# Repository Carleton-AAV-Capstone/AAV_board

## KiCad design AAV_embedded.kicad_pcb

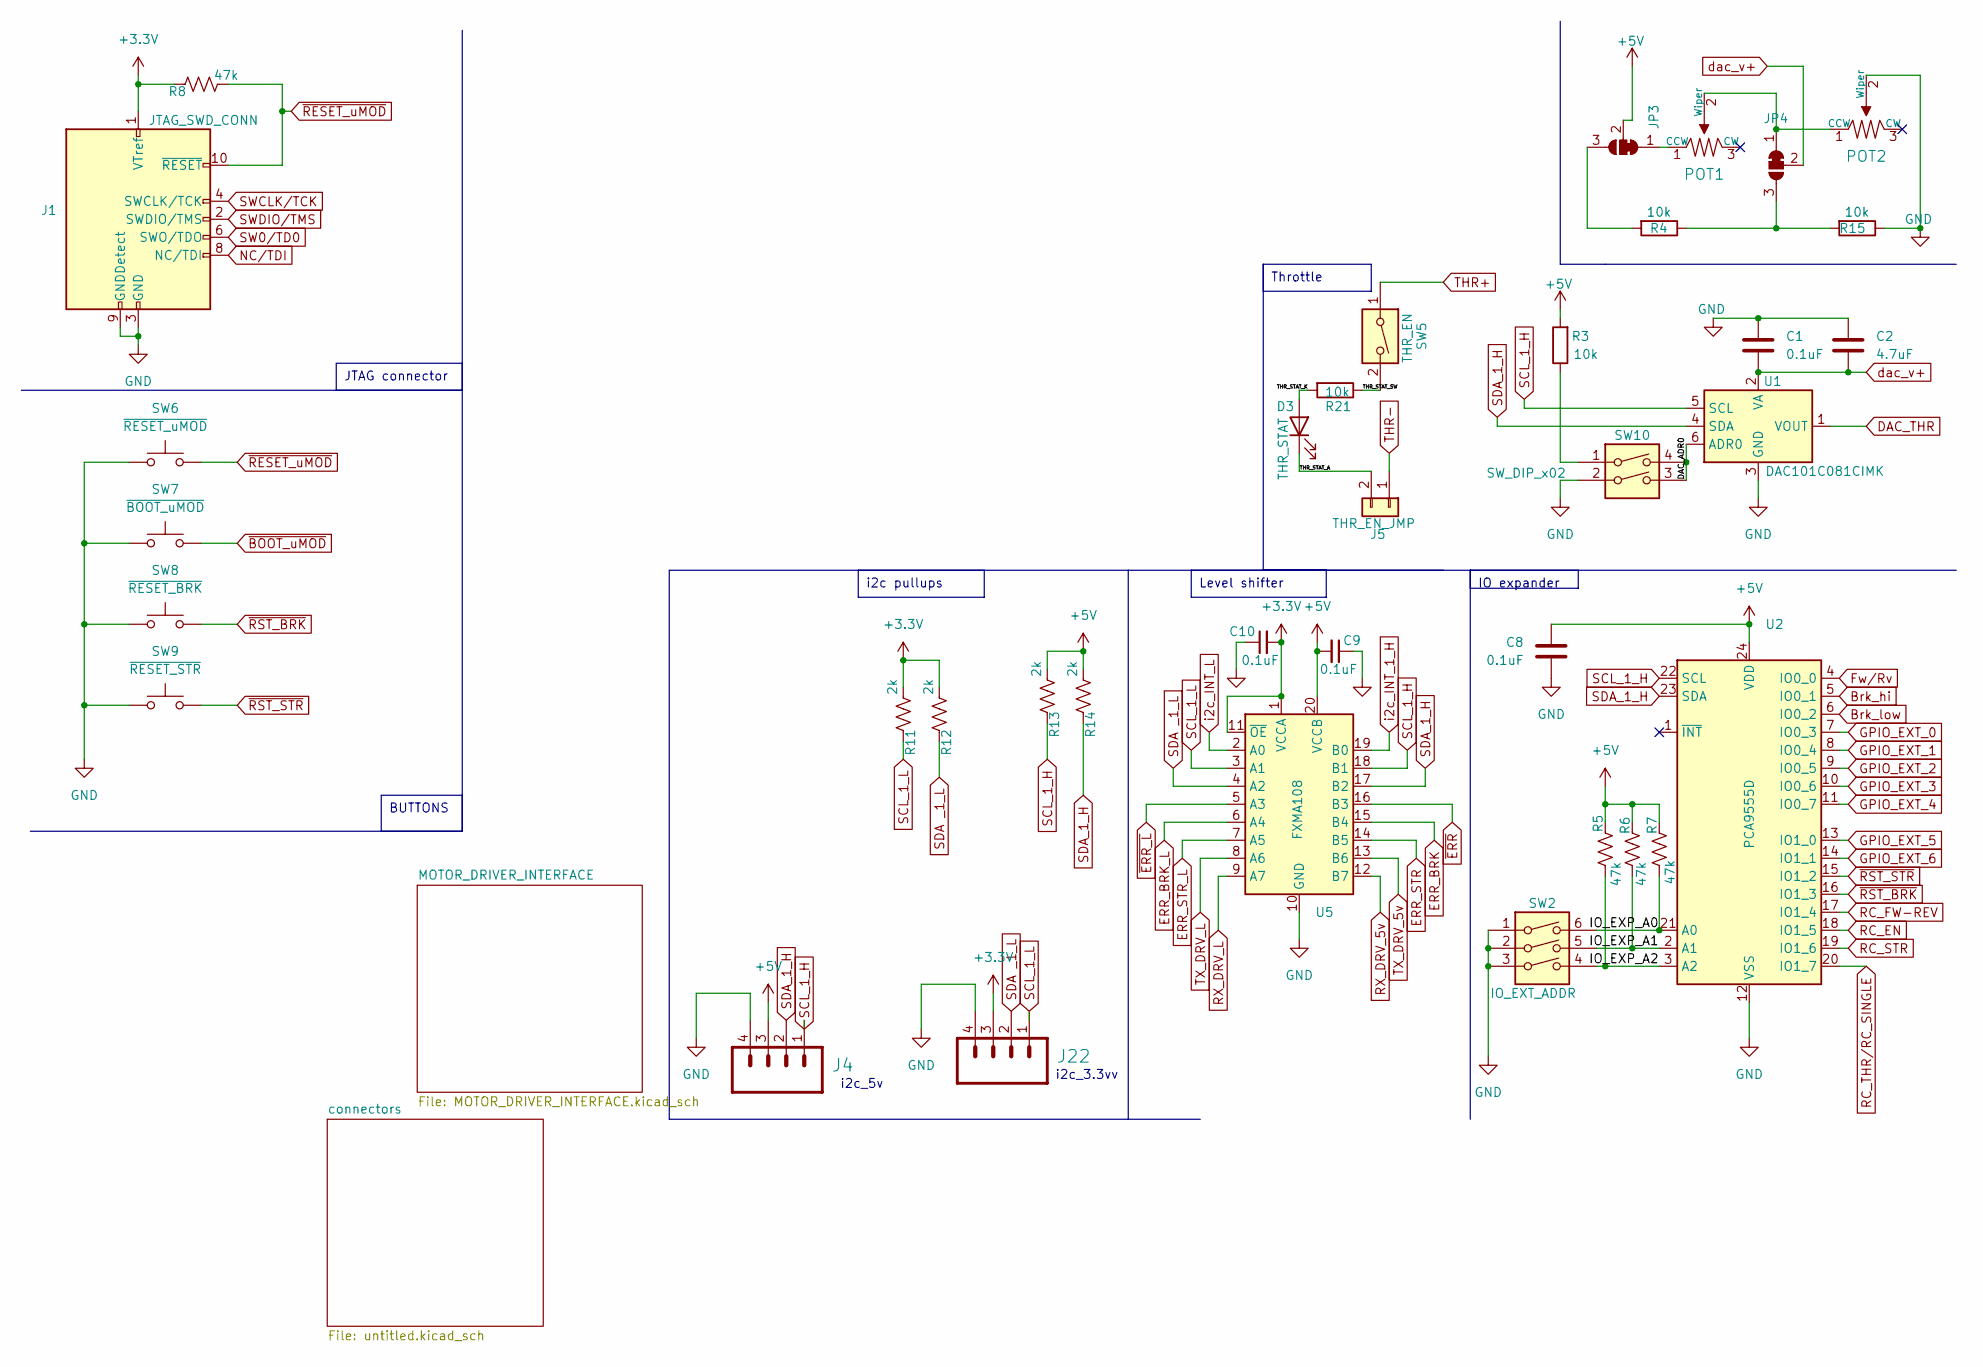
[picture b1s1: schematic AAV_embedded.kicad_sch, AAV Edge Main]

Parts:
C1, C8, C9, C10: 0.1uF; C_1206_3216Metric
C2: 4.7uF; C_1206_3216Metric
D3: THR_STAT; LED_0805_2012Metric
J1: JTAG_SWD_CONN; PinHeader_2x05_P1.27mm_Horizontal
J4, J22: JST-4-PTH
J5: THR_EN_JMP; PinHeader_1x02_P1.27mm_Horizontal; Part Number 1-0201FBV0T
JP3: POT_HIGH_BYPASS; SolderJumper-3_P1.3mm_Bridged12_Pad1.0x1.5mm
JP4: POT_LOW_BYPASS; SolderJumper-3_P1.3mm_Bridged12_Pad1.0x1.5mm
POT1, POT2: TC33X-2-103E; Potentiometer_Bourns_3266W_Vertical; MPN TC33X-2-103E; Digi-Key_PN TC33X-103ETR-ND
R3, R4, R15, R21: 10k; R_1206_3216Metric
R5, R6, R7, R8: 47k; R_1206_3216Metric
R11, R12, R13, R14: 2k; R_1206_3216Metric
SW2: IO_EXT_ADDR; SW_DIP_SPSTx03_Slide_6.7x9.18mm_W6.73mm_P2.54mm_LowProfile_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
SW5: THR_EN; SW_DIP_SPSTx01_Slide_6.7x4.1mm_W6.73mm_P2.54mm_LowProfile_J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
SW6: ~{RESET_uMOD}; SW_Push_SPST_NO_Alps_SKRK
SW7: ~{BOOT_uMOD}; SW_Push_SPST_NO_Alps_SKRK
SW8: ~{RESET_BRK}; SW_Push_SPST_NO_Alps_SKRK
SW9: ~{RESET_STR}; SW_Push_SPST_NO_Alps_SKRK
SW10: SW_DIP_x02; SW_DIP_SPSTx02_Slide_6.7x6.64mm_W6.73mm_P2.54mm_LowProfile_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
U1: DAC101C081CIMK; SOT-23-6
U2: PCA9555D; SOIC-24W_7.5x15.4mm_P1.27mm
U5: FXMA108; WQFN-20-1EP_2.5x4.5mm_P0.5mm_EP1x2.9mm

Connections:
+3.3V: C10.2, J1.1 (VTref), J22.3, R8.1, R11.2, R12.2, U5.1 (VCCA), U5.11 (~OE); also elsewhere on the board
+5V: C8.2, C9.2, J4.3, JP3.2 (C), R3.2, R5.1, R6.1, R7.1, R13.2, R14.2, U2.24 (VDD), U5.20 (VCCB); also elsewhere on the board
/DAC_ADR0: SW10.3, SW10.4, U1.6 (ADR0)
/IO_EXP_A0: R7.2, SW2.6, U2.21 (A0)
/IO_EXP_A1: R6.2, SW2.5, U2.2 (A1)
/IO_EXP_A2: R5.2, SW2.4, U2.3 (A2)
/THR_STAT_A: D3.1 (K), J5.2
/THR_STAT_K: D3.2 (A), R21.2
/THR_STAT_SW: R21.1, SW5.2
Brk_hi: U2.5 (IO0_1); also elsewhere on the board
Brk_low: U2.6 (IO0_2); also elsewhere on the board
DAC_THR: U1.1 (VOUT); also elsewhere on the board
ERR_BRK: U5.15 (B4); also elsewhere on the board
ERR_BRK_L: U5.6 (A4)
ERR_STR: U5.14 (B5); also elsewhere on the board
ERR_STR_L: U5.7 (A5)
Fw/Rv: U2.4 (IO0_0); also elsewhere on the board
GND: C1.1, C2.1, C8.1, C9.1, C10.1, J1.3 (GND), J1.5 (GND), J1.9 (GNDDetect), J4.4, J22.4, POT2.2 (Wiper), R15.1, SW2.1, SW2.2, SW2.3, SW6.1, SW7.1, SW8.1, SW9.1, SW10.2, U1.3 (GND), U2.12 (VSS), U5.10 (GND); also elsewhere on the board
GPIO_EXT_0: U2.7 (IO0_3); also elsewhere on the board
GPIO_EXT_1: U2.8 (IO0_4); also elsewhere on the board
GPIO_EXT_2: U2.9 (IO0_5); also elsewhere on the board
GPIO_EXT_3: U2.10 (IO0_6); also elsewhere on the board
GPIO_EXT_4: U2.11 (IO0_7); also elsewhere on the board
GPIO_EXT_5: U2.13 (IO1_0); also elsewhere on the board
GPIO_EXT_6: U2.14 (IO1_1)
NC/TDI: J1.8 (NC/TDI)
unnamed: JP3.1 (A), POT1.1 (CCW)
unnamed: JP3.3 (B), R4.2
unnamed: JP4.1 (A), POT1.2 (Wiper), POT2.1 (CCW)
unnamed: JP4.3 (B), R4.1, R15.2
unnamed: R3.1, SW10.1
RC_EN: U2.18 (IO1_5)
RC_FW-REV: U2.17 (IO1_4)
RC_STR: U2.19 (IO1_6)
RC_THR/RC_SINGLE: U2.20 (IO1_7)
RX_DRV_5v: U5.12 (B7); also elsewhere on the board
RX_DRV_L: U5.9 (A7); also elsewhere on the board
SCL_1_H: J4.1, R13.1, U1.5 (SCL), U2.22 (SCL), U5.18 (B1)
SCL_1_L: J22.1, R11.1, U5.3 (A1); also elsewhere on the board
SDA _1_L: J22.2, R12.1, U5.4 (A2); also elsewhere on the board
SDA_1_H: J4.2, R14.1, U1.4 (SDA), U2.23 (SDA), U5.17 (B2)
SW0/TD0: J1.6 (SWO/TDO)
SWCLK/TCK: J1.4 (SWCLK/TCK); also elsewhere on the board
SWDIO/TMS: J1.2 (SWDIO/TMS); also elsewhere on the board
THR+: SW5.1; also elsewhere on the board
THR-: J5.1; also elsewhere on the board
TX_DRV_5v: U5.13 (B6); also elsewhere on the board
TX_DRV_L: U5.8 (A6); also elsewhere on the board
dac_v+: C1.2, C2.2, JP4.2 (C), U1.2 (VA)
i2c_INT_1_H: U5.19 (B0)
i2c_INT_L: U5.2 (A0); also elsewhere on the board
~BOOT_uMOD: SW7.2; also elsewhere on the board
~E-STOP: U5.5 (A3); also elsewhere on the board
~ERR: U5.16 (B3)
~RESET_uMOD: J1.10 (~RESET), R8.2, SW6.2; also elsewhere on the board
~RST_BRK: SW8.2, U2.16 (IO1_3); also elsewhere on the board
~RST_STR: SW9.2, U2.15 (IO1_2); also elsewhere on the board

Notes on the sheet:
Throttle
IO expander
JTAG connector
i2c pullups
Level shifter
BUTTONS
i2c_5v
i2c_3.3vv

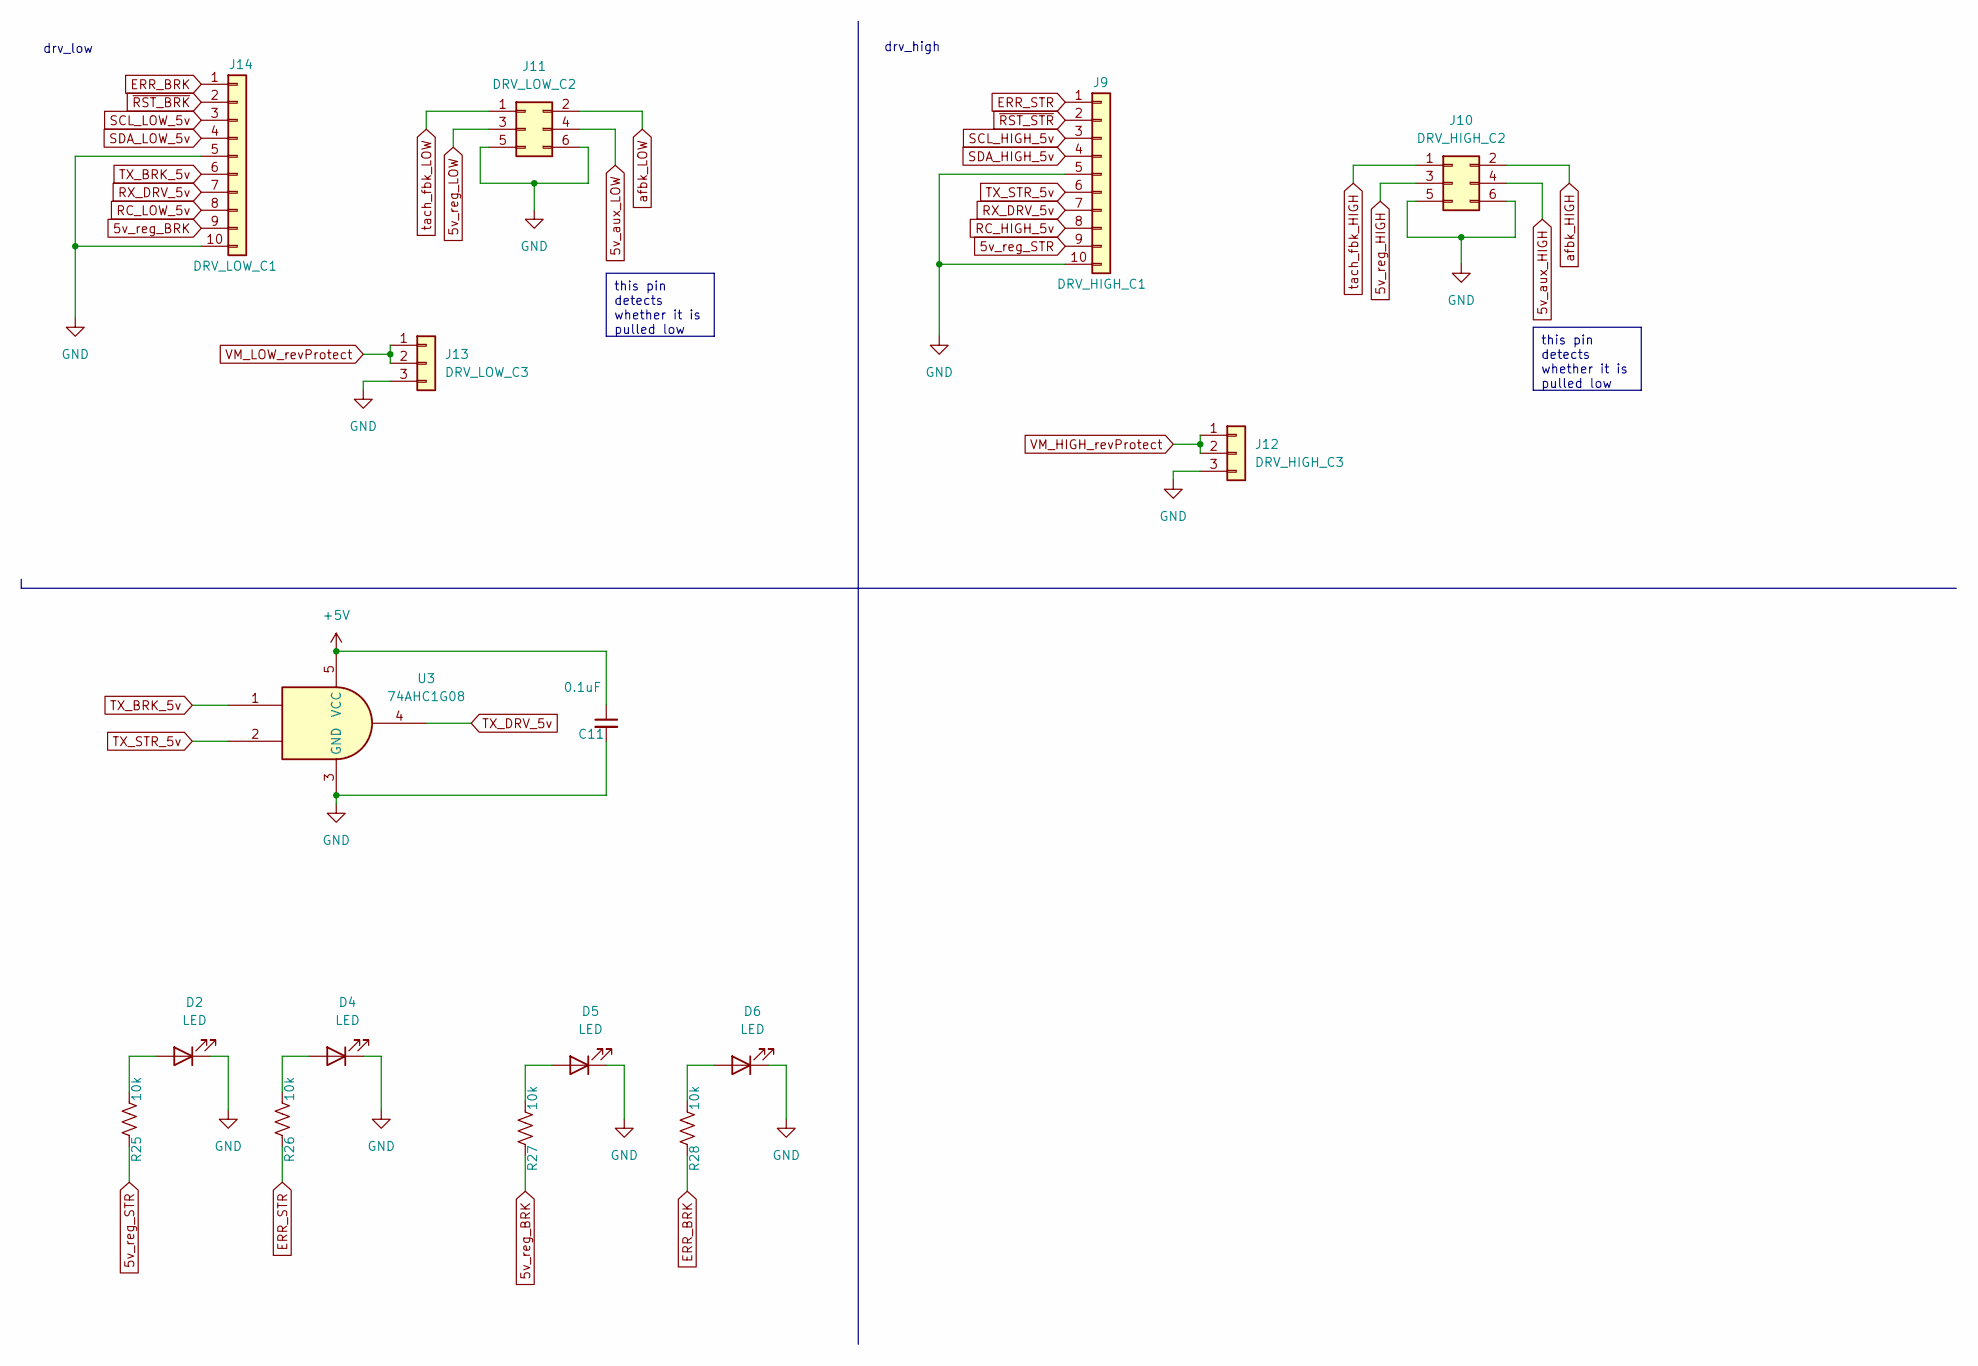
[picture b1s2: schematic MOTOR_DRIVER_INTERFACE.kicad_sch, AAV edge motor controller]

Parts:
C11: 0.1uF; C_1206_3216Metric
D2, D4, D5, D6: LED; LED_0805_2012Metric
J9: DRV_HIGH_C1; PinSocket_1x10_P2.54mm_Vertical
J10: DRV_HIGH_C2; PinSocket_2x03_P2.54mm_Vertical; Part Number LL1009-2A, 2.54MM 2*3PIN HEADER,LENGTH=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
J11: DRV_LOW_C2; PinSocket_2x03_P2.54mm_Vertical; Part Number LL1009-2A, 2.54MM 2*3PIN HEADER,LENGTH=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
J12: DRV_HIGH_C3; PinSocket_1x03_P2.54mm_Vertical; Part Number 1-0301FBV0T
J13: DRV_LOW_C3; PinSocket_1x03_P2.54mm_Vertical; Part Number 1-0301FBV0T
J14: DRV_LOW_C1; PinSocket_1x10_P2.54mm_Vertical
R25, R26, R27, R28: 10k; R_1206_3216Metric
U3: 74AHC1G08; SOT-23-5_HandSoldering

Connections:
5v_aux_HIGH: J10.4 (GND)
5v_aux_LOW: J11.4 (GND)
5v_reg_BRK: J14.9, R27.1
5v_reg_HIGH: J10.3 (GND)
5v_reg_LOW: J11.3 (GND)
5v_reg_STR: J9.9, R25.1
+5V: C11.1, U3.5 (VCC); also elsewhere on the board
ERR_BRK: J14.1, R28.1; also elsewhere on the board
ERR_STR: J9.1, R26.1; also elsewhere on the board
GND: C11.2, D2.1 (K), D4.1 (K), D5.1 (K), D6.1 (K), J9.5, J9.10, J10.5 (GND), J10.6 (GND), J11.5 (GND), J11.6 (GND), J12.3, J13.3, J14.5, J14.10, U3.3 (GND); also elsewhere on the board
unnamed: D2.2 (A), R25.2
unnamed: D4.2 (A), R26.2
unnamed: D5.2 (A), R27.2
unnamed: D6.2 (A), R28.2
RC_HIGH_5v: J9.8
RC_LOW_5v: J14.8
RX_DRV_5v: J9.7, J14.7; also elsewhere on the board
SCL_HIGH_5v: J9.3
SCL_LOW_5v: J14.3
SDA_HIGH_5v: J9.4
SDA_LOW_5v: J14.4
TX_BRK_5v: J14.6, U3.1
TX_DRV_5v: U3.4; also elsewhere on the board
TX_STR_5v: J9.6, U3.2
VM_HIGH_revProtect: J12.1, J12.2
VM_LOW_revProtect: J13.1, J13.2
afbk_HIGH: J10.2 (+12V)
afbk_LOW: J11.2 (+12V)
tach_fbk_HIGH: J10.1 (+12V)
tach_fbk_LOW: J11.1 (+12V)
~RST_BRK: J14.2; also elsewhere on the board
~RST_STR: J9.2; also elsewhere on the board

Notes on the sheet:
this pin detects whether it is pulled low
drv_high
drv_low

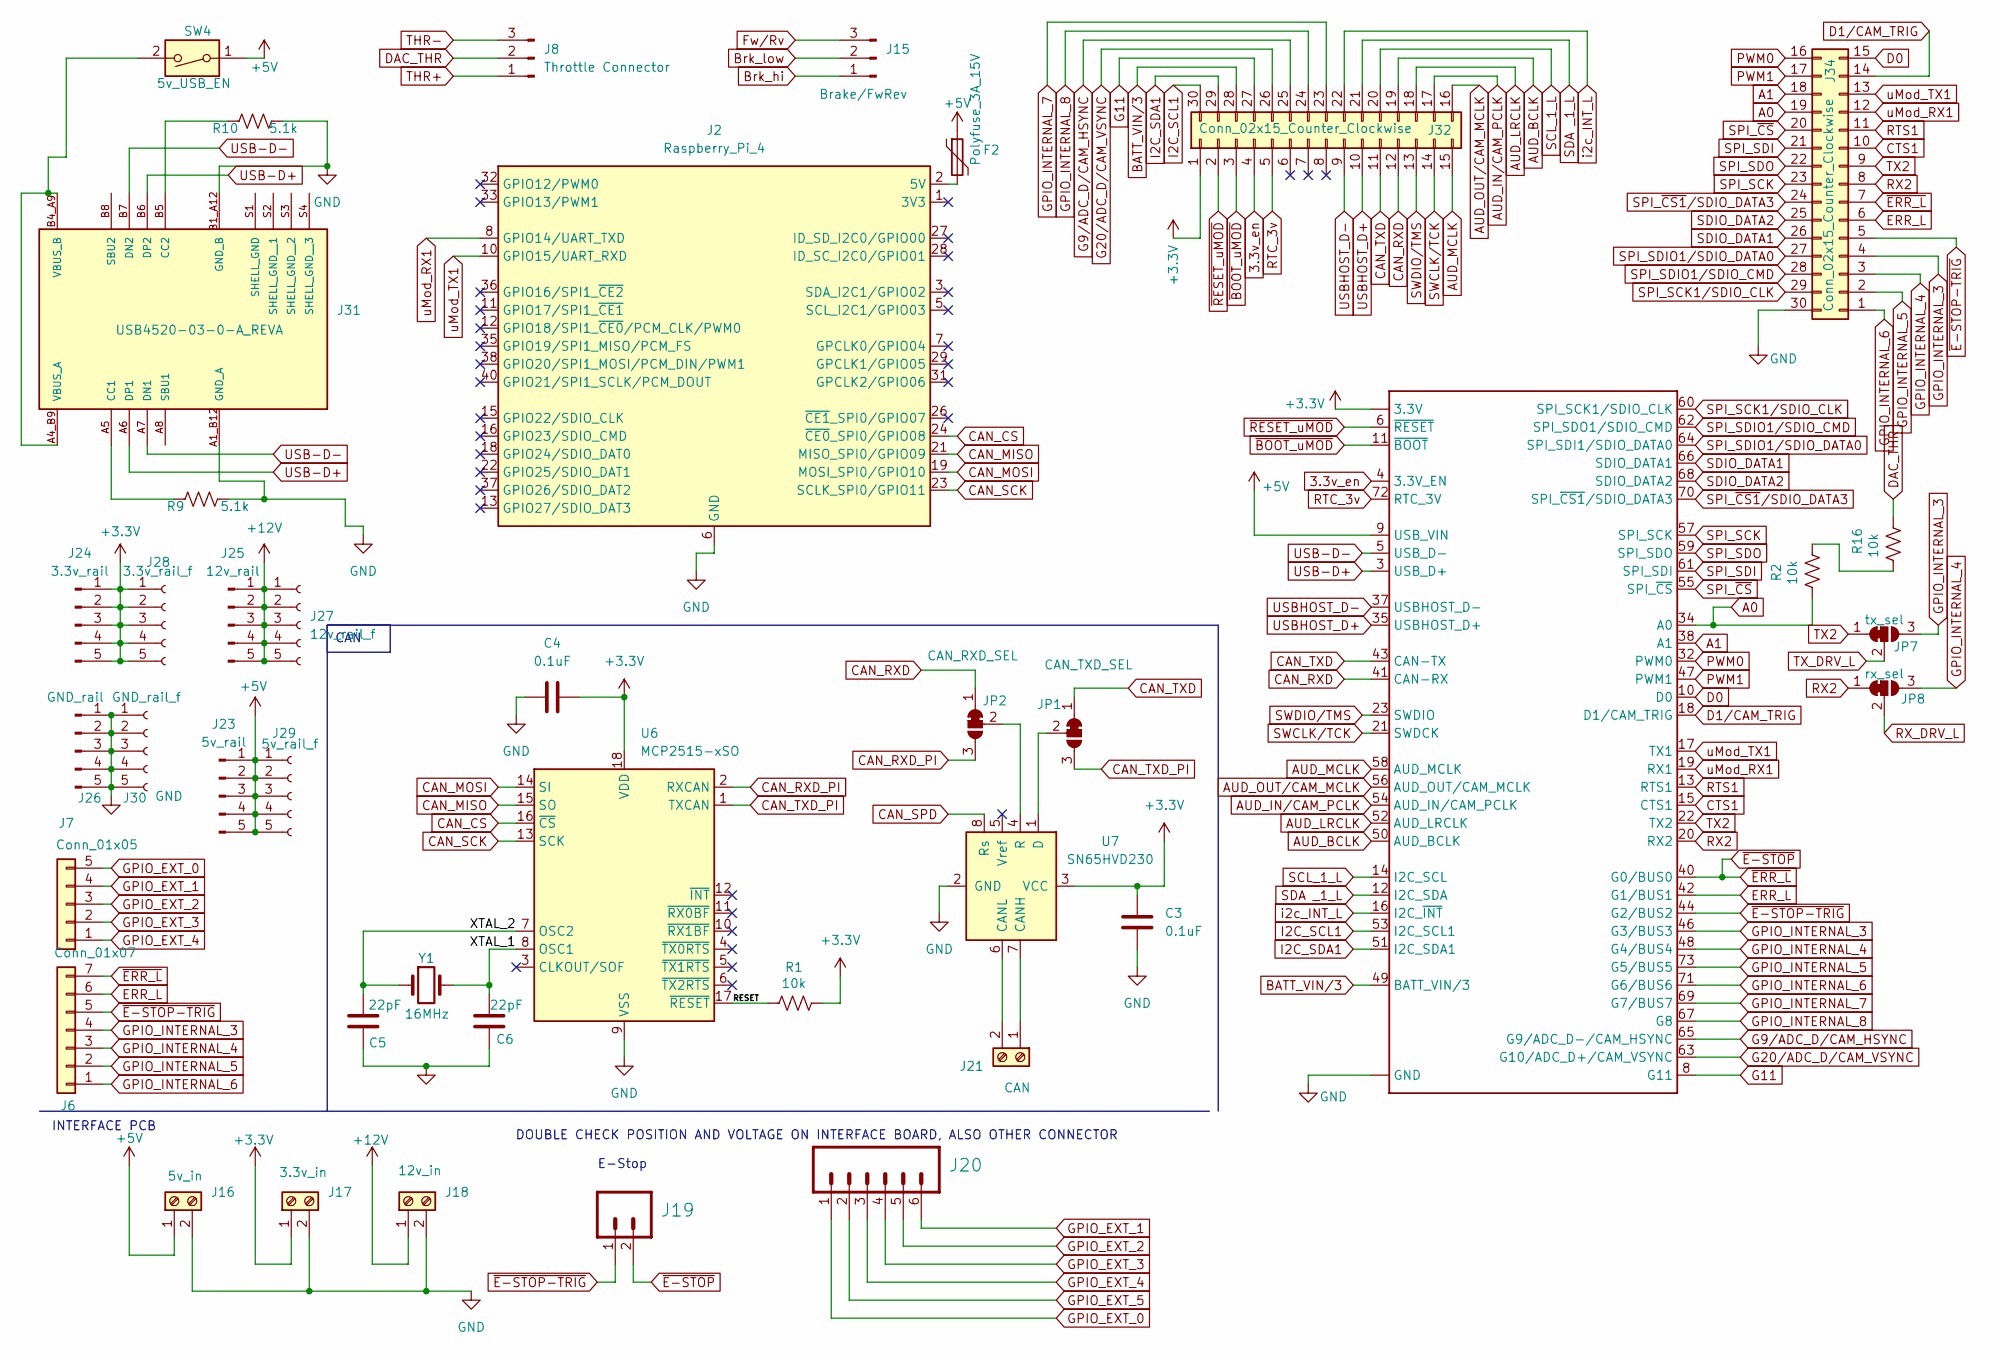
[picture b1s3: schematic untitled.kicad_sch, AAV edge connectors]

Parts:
C3, C4: 0.1uF; C_1206_3216Metric
C5, C6: 22pF; C_1206_3216Metric
F2: Polyfuse_3A_15V; Fuse_1812_4532Metric; Part Number miniSMDC150F/24; JLCPCB ID C207070
J2: Raspberry_Pi_4; PinSocket_2x20_P2.54mm_Vertical
J6: Conn_01x07; PinHeader_1x07_P2.54mm_Vertical
J7: Conn_01x05; PinHeader_1x05_P2.54mm_Vertical
J8: Throttle Connector; PinHeader_1x03_P2.54mm_Horizontal
J15: Brake/FwRev; PinHeader_1x03_P2.54mm_Horizontal
J16: 5v_in; TerminalBlock_MetzConnect_Type011_RT05502HBWC_1x02_P5.00mm_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
J17: 3.3v_in; TerminalBlock_MetzConnect_Type011_RT05502HBWC_1x02_P5.00mm_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
J18: 12v_in; TerminalBlock_MetzConnect_Type011_RT05502HBWC_1x02_P5.00mm_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
J19: JST-2-PTH
J20: JST-6-SMD-1.25MM-LOCKING
J21: CAN; JST_EH_B2B-EH-A_1x02_P2.50mm_Vertical
J23: 5v_rail; PinHeader_1x05_P2.54mm_Vertical
J24: 3.3v_rail; PinHeader_1x05_P2.54mm_Vertical
J25: 12v_rail; PinHeader_1x05_P2.54mm_Vertical
J26: GND_rail; PinHeader_1x05_P2.54mm_Vertical
J27: 12v_rail_f; PinSocket_1x05_P2.54mm_Vertical
J28: 3.3v_rail_f; PinSocket_1x05_P2.54mm_Vertical
J29: 5v_rail_f; PinSocket_1x05_P2.54mm_Vertical
J30: GND_rail_f; PinSocket_1x05_P2.54mm_Vertical
J31: USB4520-03-0-A_REVA; GCT_USB4105-GF-A; PARTREV A
J32, J34: Conn_02x15_Counter_Clockwise; PinHeader_2x15_P2.54mm_Vertical
J33: M.2-CONNECTOR-E
JP1: CAN_TXD_SEL; SolderJumper-3_P1.3mm_Bridged12_Pad1.0x1.5mm
JP2: CAN_RXD_SEL; SolderJumper-3_P1.3mm_Bridged12_Pad1.0x1.5mm
JP7: tx_sel; SolderJumper-3_P1.3mm_Bridged12_Pad1.0x1.5mm
JP8: rx_sel; SolderJumper-3_P1.3mm_Bridged12_Pad1.0x1.5mm
R1, R2, R16: 10k; R_1206_3216Metric
R9, R10: 5.1k; R_1206_3216Metric
SW4: 5v_USB_EN; SW_DIP_SPSTx01_Slide_6.7x4.1mm_W6.73mm_P2.54mm_LowProfile_J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
U6: MCP2515-xSO; SOIC-18W_7.5x11.6mm_P1.27mm
U7: SN65HVD230; SOIC-8_3.9x4.9mm_P1.27mm
Y1: 16MHz; Crystal_HC18-U_Vertical

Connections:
3.3v_en: J32.4, J33.4 (3.3V_EN)
+3.3V: C3.1, C4.1, J17.1, J24.1, J24.2, J24.3, J24.4, J24.5, J28.1, J28.2, J28.3, J28.4, J28.5, J32.1, J33.2 (3.3V), J33.74 (3.3V), R1.1, U6.18 (VDD), U7.3 (VCC); also elsewhere on the board
+5V: F2.1, J16.1, J23.1, J23.2, J23.3, J23.4, J23.5, J29.1, J29.2, J29.3, J29.4, J29.5, J33.9 (USB_VIN), SW4.1; also elsewhere on the board
+12V: J18.1, J25.1, J25.2, J25.3, J25.4, J25.5, J27.1, J27.2, J27.3, J27.4, J27.5
/connectors/RESET: R1.2, U6.17 (~RESET)
/connectors/XTAL_1: C6.2, U6.8 (OSC1), Y1.2
/connectors/XTAL_2: C5.1, U6.7 (OSC2), Y1.1
A0: J33.34 (A0), J34.19, R2.2
A1: J33.38 (A1), J34.18
AUD_BCLK: J32.19, J33.50 (AUD_BCLK)
AUD_IN/CAM_PCLK: J32.17, J33.54 (AUD_IN/CAM_PCLK)
AUD_LRCLK: J32.18, J33.52 (AUD_LRCLK)
AUD_MCLK: J32.15, J33.58 (AUD_MCLK)
AUD_OUT/CAM_MCLK: J32.16, J33.56 (AUD_OUT/CAM_MCLK)
BATT_VIN/3: J32.28, J33.49 (BATT_VIN/3)
Brk_hi: J15.1; also elsewhere on the board
Brk_low: J15.2; also elsewhere on the board
CAN_CS: J2.24 (~CE0_SPI0/GPIO08), U6.16 (~CS)
CAN_MISO: J2.21 (MISO_SPI0/GPIO09), U6.15 (SO)
CAN_MOSI: J2.19 (MOSI_SPI0/GPIO10), U6.14 (SI)
CAN_RXD: J32.12, J33.41 (CAN-RX), JP2.1 (A)
CAN_RXD_PI: JP2.3 (B), U6.2 (RXCAN)
CAN_SCK: J2.23 (SCLK_SPI0/GPIO11), U6.13 (SCK)
CAN_SPD: U7.8 (Rs)
CAN_TXD: J32.11, J33.43 (CAN-TX), JP1.1 (A)
CAN_TXD_PI: JP1.3 (B), U6.1 (TXCAN)
CTS1: J33.15 (CTS1), J34.10
D0: J33.10 (D0), J34.15
D1/CAM_TRIG: J33.18 (D1/CAM_TRIG), J34.14
DAC_THR: J8.2, R16.1; also elsewhere on the board
ERR_L: J6.6, J33.42 (G1/BUS1), J34.6
Fw/Rv: J15.3; also elsewhere on the board
G9/ADC_D/CAM_HSYNC: J32.25, J33.65 (G9/ADC_D-/CAM_HSYNC)
G11: J32.27, J33.8 (G11)
G20/ADC_D/CAM_VSYNC: J32.26, J33.63 (G10/ADC_D+/CAM_VSYNC)
GND: C3.2, C4.2, C5.2, C6.1, J2.6 (GND), J2.9 (GND), J2.14 (GND), J2.20 (GND), J2.25 (GND), J2.30 (GND), J2.34 (GND), J2.39 (GND), J16.2, J17.2, J18.2, J26.1, J26.2, J26.3, J26.4, J26.5, J30.1, J30.2, J30.3, J30.4, J30.5, J31.A1_B12 (GND_A), J31.B1_A12 (GND_B), J33.1 (GND), J33.7 (GND), J33.33 (GND), J33.36 (GND), J33.39 (GND), J33.45 (GND), J33.75 (GND), J34.30, R9.2, R10.2, U6.9 (VSS), U7.2 (GND); also elsewhere on the board
GPIO_EXT_0: J7.5, J20.1; also elsewhere on the board
GPIO_EXT_1: J7.4, J20.6; also elsewhere on the board
GPIO_EXT_2: J7.3, J20.5; also elsewhere on the board
GPIO_EXT_3: J7.2, J20.4; also elsewhere on the board
GPIO_EXT_4: J7.1, J20.3; also elsewhere on the board
GPIO_EXT_5: J20.2; also elsewhere on the board
GPIO_INTERNAL_3: J6.4, J33.46 (G3/BUS3), J34.4, JP7.3 (B)
GPIO_INTERNAL_4: J6.3, J33.48 (G4/BUS4), J34.3, JP8.3 (B)
GPIO_INTERNAL_5: J6.2, J33.73 (G5/BUS5), J34.2
GPIO_INTERNAL_6: J6.1, J33.71 (G6/BUS6), J34.1
GPIO_INTERNAL_7: J32.23, J33.69 (G7/BUS7)
GPIO_INTERNAL_8: J32.24, J33.67 (G8)
I2C_SCL1: J32.30, J33.53 (I2C_SCL1)
I2C_SDA1: J32.29, J33.51 (I2C_SDA1)
unnamed: F2.2, J2.2 (5V), J2.4 (5V)
unnamed: J21.1, U7.7 (CANH)
unnamed: J21.2, U7.6 (CANL)
unnamed: J31.A5 (CC1), R9.1
unnamed: J31.B5 (CC2), R10.1
unnamed: J31.A4_B9 (VBUS_A), J31.B4_A9 (VBUS_B), SW4.2
unnamed: JP1.2 (C), U7.1 (D)
unnamed: JP2.2 (C), U7.4 (R)
unnamed: R2.1, R16.2
PWM0: J33.32 (PWM0), J34.16
PWM1: J33.47 (PWM1), J34.17
RTC_3v: J32.5, J33.72 (RTC_3V)
RTS1: J33.13 (RTS1), J34.11
RX2: J33.20 (RX2), J34.8, JP8.1 (A)
RX_DRV_L: JP8.2 (C); also elsewhere on the board
SCL_1_L: J32.20, J33.14 (I2C_SCL); also elsewhere on the board
SDA _1_L: J32.21, J33.12 (I2C_SDA); also elsewhere on the board
SDIO_DATA1: J33.66 (SDIO_DATA1), J34.26
SDIO_DATA2: J33.68 (SDIO_DATA2), J34.25
SPI_SCK: J33.57 (SPI_SCK), J34.23
SPI_SCK1/SDIO_CLK: J33.60 (SPI_SCK1/SDIO_CLK), J34.29
SPI_SDI: J33.61 (SPI_SDI), J34.21
SPI_SDIO1/SDIO_CMD: J33.62 (SPI_SDO1/SDIO_CMD), J34.28
SPI_SDIO1/SDIO_DATA0: J33.64 (SPI_SDI1/SDIO_DATA0), J34.27
SPI_SDO: J33.59 (SPI_SDO), J34.22
SPI_~CS1/SDIO_DATA3: J33.70 (SPI_~CS1/SDIO_DATA3), J34.24
SPI_~CS: J33.55 (SPI_~CS), J34.20
SWCLK/TCK: J32.14, J33.21 (SWDCK); also elsewhere on the board
SWDIO/TMS: J32.13, J33.23 (SWDIO); also elsewhere on the board
THR+: J8.1; also elsewhere on the board
THR-: J8.3; also elsewhere on the board
TX2: J33.22 (TX2), J34.9, JP7.1 (A)
TX_DRV_L: JP7.2 (C); also elsewhere on the board
USB-D+: J31.A6 (DP1), J31.B6 (DP2), J33.3 (USB_D+)
USB-D-: J31.A7 (DN1), J31.B7 (DN2), J33.5 (USB_D-)
USBHOST_D+: J32.10, J33.35 (USBHOST_D+)
USBHOST_D-: J32.9, J33.37 (USBHOST_D-)
i2c_INT_L: J32.22, J33.16 (I2C_~INT); also elsewhere on the board
uMod_RX1: J2.8 (GPIO14/UART_TXD), J33.19 (RX1), J34.12
uMod_TX1: J2.10 (GPIO15/UART_RXD), J33.17 (TX1), J34.13
~BOOT_uMOD: J32.3, J33.11 (~BOOT); also elsewhere on the board
~E-STOP-TRIG: J6.5, J19.1, J33.44 (G2/BUS2), J34.5
~E-STOP: J6.7, J19.2, J33.40 (G0/BUS0), J34.7; also elsewhere on the board
~RESET_uMOD: J32.2, J33.6 (~RESET); also elsewhere on the board

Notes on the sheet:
CAN
E-Stop
DOUBLE CHECK POSITION AND VOLTAGE ON INTERFACE BOARD, ALSO OTHER CONNECTOR
INTERFACE PCB

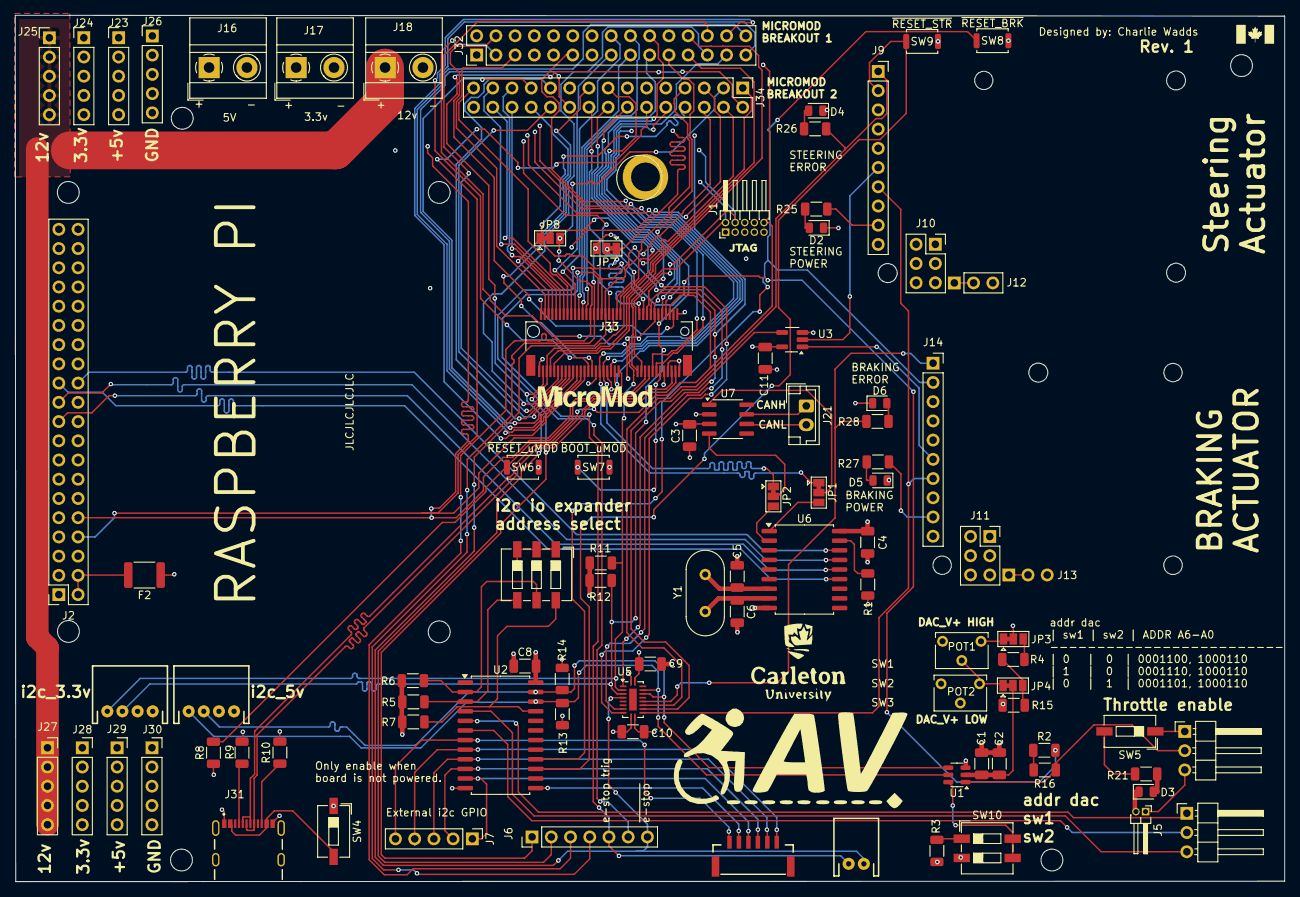
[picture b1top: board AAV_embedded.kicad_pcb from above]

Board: 4 copper layers, 167.7 x 114.4 mm, 93 parts (0 on the bottom side), 124 nets.

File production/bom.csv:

"Designator","Footprint","Quantity","Value","LCSC Part #"
"_3","JTAG_TO","1","",""
"_2","STAND-OFF-REFLOW-M2.5","1","",""
"","MICROMOD_LOGO_.6","1","",""
"C1, C10, C11, C3, C4, C8, C9","1206","7","0.1uF",""
"C2","1206","1","4.7uF",""
"C5, C6","1206","2","22pF",""
"D2, D4, D5, D6","805","4","LED",""
"D3","805","1","THR_STAT",""
"F2","1812","1","Polyfuse_3A_15V",""
"J1","PinHeader_2x05_P1.27mm_Horizontal","1","JTAG_SWD_CONN",""
"J10","PinSocket_2x03_P2.54mm_Vertical","1","DRV_HIGH_C2",""
"J11","PinSocket_2x03_P2.54mm_Vertical","1","DRV_LOW_C2",""
"J12","PinSocket_1x03_P2.54mm_Vertical","1","DRV_HIGH_C3",""
"J13","PinSocket_1x03_P2.54mm_Vertical","1","DRV_LOW_C3",""
"J14","PinSocket_1x10_P2.54mm_Vertical","1","DRV_LOW_C1",""
"J15","PinHeader_1x03_P2.54mm_Horizontal","1","Brake/FwRev",""
"J16","TerminalBlock_MetzConnect_Type011_RT05502HBWC_1x02_P5.00mm_Horizontal","1","5v_in",""
"J17","TerminalBlock_MetzConnect_Type011_RT05502HBWC_1x02_P5.00mm_Horizontal","1","3.3v_in",""
"J18","TerminalBlock_MetzConnect_Type011_RT05502HBWC_1x02_P5.00mm_Horizontal","1","12v_in",""
"J19","JST-2-PTH","1","~",""
"J2","PinSocket_2x20_P2.54mm_Vertical","1","Raspberry_Pi_4",""
"J20","JST-6-SMD-1.25MM-LOCKING","1","~",""
"J21","JST_EH_B2B-EH-A_1x02_P2.50mm_Vertical","1","CAN",""
"J22, J4","JST-4-PTH","2","~",""
"J23","PinHeader_1x05_P2.54mm_Vertical","1","5v_rail",""
"J27","PinSocket_1x05_P2.54mm_Vertical","1","12v_rail_f",""
"J28","PinSocket_1x05_P2.54mm_Vertical","1","3.3v_rail_f",""
"J29","PinSocket_1x05_P2.54mm_Vertical","1","5v_rail_f",""
"J30","PinSocket_1x05_P2.54mm_Vertical","1","GND_rail_f",""
"J31","GCT_USB4105-GF-A","1","USB4520-03-0-A_REVA",""
"J32, J34","PinHeader_2x15_P2.54mm_Vertical","2","Conn_02x15_Counter_Clockwise",""
"J33","M.2-CONNECTOR-E","1","~",""
"J5","PinHeader_1x02_P1.27mm_Horizontal","1","THR_EN_JMP",""
"J6","PinHeader_1x07_P2.54mm_Vertical","1","Conn_01x07",""
"J7","PinHeader_1x05_P2.54mm_Vertical","1","Conn_01x05",""
"J8","PinHeader_1x03_P2.54mm_Horizontal","1","Throttle Connector",""
"J9","PinSocket_1x10_P2.54mm_Vertical","1","DRV_HIGH_C1",""
"POT1, POT2","Potentiometer_Bourns_3266W_Vertical","2","TC33X-2-103E","TC33X-2-103E"
"R1, R15, R16, R2, R21, R25, R26, R27, R28, R3, R4","1206","11","10k",""
"R10, R9","1206","2","5.1k",""
"R11, R12, R13, R14","1206","4","2k",""
"R5, R6, R7, R8","1206","4","47k",""
"SW10","SW_DIP_SPSTx02_Slide_6.7x6.64mm_W6.73mm_P2.54mm_LowProfile_JPin","1","SW_DIP_x02",""
"SW2","SW_DIP_SPSTx03_Slide_6.7x9.18mm_W6.73mm_P2.54mm_LowProfile_JPin","1","IO_EXT_ADDR",""
"SW4","SW_DIP_SPSTx01_Slide_6.7x4.1mm_W6.73mm_P2.54mm_LowProfile_JPin","1","5v_USB_EN",""
"SW5","SW_DIP_SPSTx01_Slide_6.7x4.1mm_W6.73mm_P2.54mm_LowProfile_JPin","1","THR_EN",""
"SW6","SW_Push_SPST_NO_Alps_SKRK","1","~{RESET_uMOD}",""
"SW7","SW_Push_SPST_NO_Alps_SKRK","1","~{BOOT_uMOD}",""
"SW8","SW_Push_SPST_NO_Alps_SKRK","1","~{RESET_BRK}",""
"SW9","SW_Push_SPST_NO_Alps_SKRK","1","~{RESET_STR}",""
"U1","SOT-23-6","1","DAC101C081CIMK",""
"U2","SOIC-24W_7.5x15.4mm_P1.27mm","1","PCA9555D",""
"U3","SOT-23-5_HandSoldering","1","74AHC1G08",""
"U5","WQFN-20-1EP_2.5x4.5mm_P0.5mm_EP1x2.9mm","1","FXMA108",""
"U6","SOIC-18W_7.5x11.6mm_P1.27mm","1","MCP2515-xSO",""
"U7","SOIC-8_3.9x4.9mm_P1.27mm","1","SN65HVD230",""
"Y1","Crystal_HC18-U_Vertical","1","16MHz",""

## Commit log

2025-02-01 board layout v1
2025-02-01 add solder jumpers
2025-02-01 add more silkscreen
2025-02-01 added mounting holes
2025-02-02 i2c address fix and logo
2025-02-02 fix dac
2025-02-02 renamed design rules file so that it works
2025-02-02 Review and fixes from reliability and safety team
2025-02-03 added micromod breakout and fixed voltage divider
2025-02-03 remove dip switch table silkscreen
2025-02-03 saved
2025-02-03 add jlc tracking
2025-02-03 silkscreen
2025-02-03 Remove auto_saved_files from tracking*
2025-02-04 updated gitignore to ignore *gerber.zip
2025-02-04 pre-fab review & cleanup
2025-02-04 changed LED
2025-03-02 new branch with fixes
2025-03-02 fix level shifting in schematic
